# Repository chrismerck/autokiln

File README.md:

# autokiln
Controller for Small Wood-Drying Kilns

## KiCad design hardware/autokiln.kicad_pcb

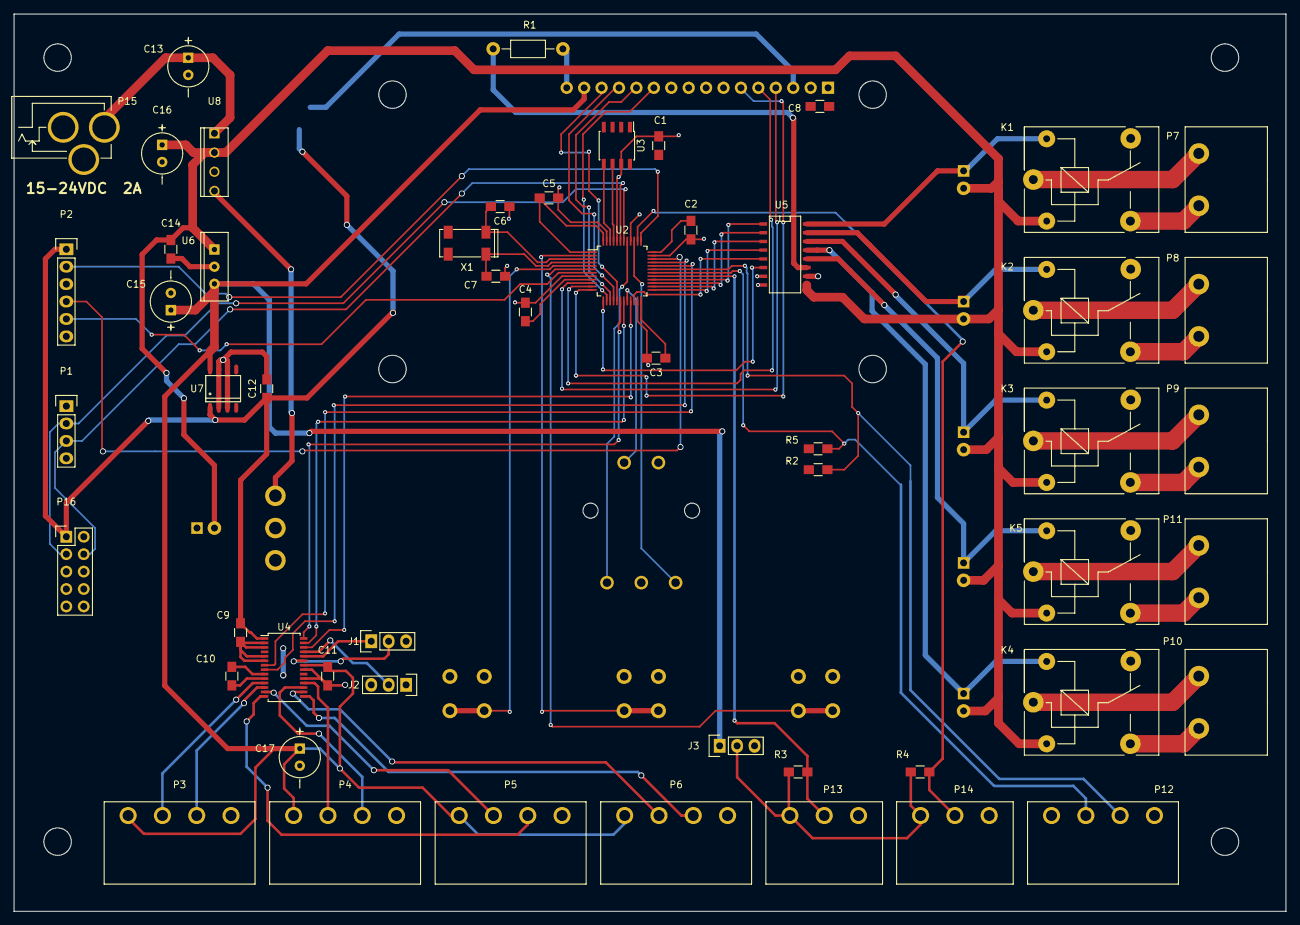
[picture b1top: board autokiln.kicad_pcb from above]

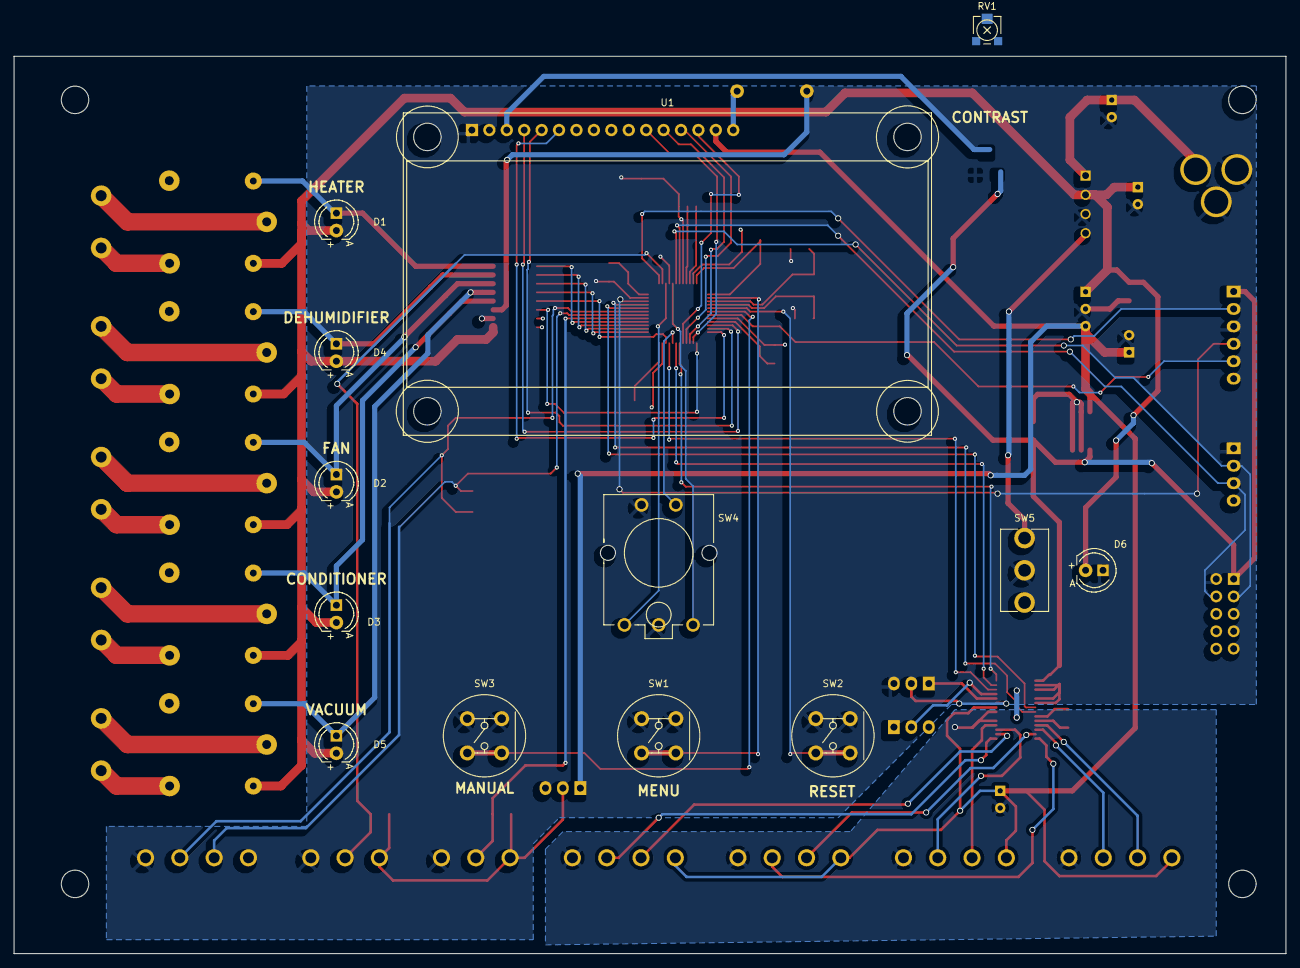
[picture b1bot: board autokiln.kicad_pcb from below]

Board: 2 copper layers, 185.4 x 130.8 mm, 67 parts (13 on the bottom side), 74 nets.

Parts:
C1, C2, C3, C5, C8, C9, C10, C11: 100nF; R_0805_HandSoldering
C4, C12, C14: 4u7; R_0805_HandSoldering
C6, C7: 10pF; R_0805_HandSoldering
C13, C15, C16, C17: 100uF; KEMET_100uF_25V
D1, D2, D3, D4, D5, D6: 12V LED; Diode_LED_5mm_round_vertical
J1: GAIN JUMPER; Pin_Header_Straight_1x03
J2: SPEED JUMPER; Pin_Header_Straight_1x03
J3: HUMID PWR; Pin_Header_Straight_1x03
K1, K2, K3, K4, K5: 12V 250VAC 10A; Relay_SANYOU_SRD_Series_Form_C
P1: DEBUG; Pin_Header_Straight_1x04
P2: SWD; Pin_Header_Straight_1x06
P3: LOAD CELL 1; ostoq047151
P4: LOAD CELL 2; ostoq047151
P5: LOAD CELL 3; ostoq047151
P6: LOAD CELL 4; ostoq047151
P7: HEATER; OSTOQ020151
P8: DEHUMIDIFIER; OSTOQ020151
P9: FAN; OSTOQ020151
P10: VACUUM; OSTOQ020151
P11: CONDITIONER; OSTOQ020151
P12: BAROM; ostoq047151
P13: HUMID1; OSTOQ037151
P14: HUMID2; OSTOQ037151
P15: VIN; CUI_PJ-002AH_DC_PWR_JACK
P16: UEXT; Pin_Header_Straight_2x05
R1: 3; Resistor_Horizontal_RM10mm
R2, R5: 4k7; R_0805_HandSoldering
R3, R4: 1k; R_0805_HandSoldering
RV1: 10K; BOURNS_TRIMMER_3303W
SW1: MENU; CK_Button_D6R
SW2: RESET; CK_Button_D6R
SW3: MANUAL; CK_Button_D6R
SW4: PEC16-4215F-S0024; BOURNS_Encoder_PEC16
SW5: PWR SWITCH; ESwitch-100SP1T1B4M2QE
U1: NHD-0420AZ-FL-YBW-33V3; NHD-0420AZ-FL-GBW-33V3
U2: STM32F070CBT6; LQFP-48_7x7mm_Pitch0.5mm
U3: 24LC512; SOIC-8_3.9x4.9mm_Pitch1.27mm
U4: ADS1234; TSSOP-28_4.4x9.7mm_Pitch0.65mm
U5: ULQ2003; SO-16-N
U6: L7805; TO-220_SG
U7: L4931; SO-8
U8: KA278R12C; TO-220F-4L
X1: 32kHz; Abracon_32KHz

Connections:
+5V: C11.1, C15.1, C17.1, J3.1, P3.1, P4.1, P5.1, P6.1, U1.15, U4.20, U4.22, U6.3, U7.8
+12V: C14.1, C16.1, D1.1, D2.1, D3.1, D4.1, D5.1, D6.1, K1.2, K2.2, K3.2, K4.2, K5.2, U5.9, U6.1, U8.2
/LoadCells/GAIN0: J1.2, U4.23
/LoadCells/LC1N: P3.3, U4.12
/LoadCells/LC1P: P3.2, U4.11
/LoadCells/LC2N: P4.3, U4.17
/LoadCells/LC2P: P4.2, U4.18
/LoadCells/LC3N: P5.3, U4.14
/LoadCells/LC3P: P5.2, U4.13
/LoadCells/LC4N: P6.3, U4.15
/LoadCells/LC4P: P6.2, U4.16
/LoadCells/SPEED: J2.2, U4.25
/Power/VDIS: SW5.1, U8.4
/Relays/DEHUM_COIL: D4.2, K2.5, U5.15
/Relays/FAN_COIL: D2.2, K3.5, U5.14
/Relays/HEATER_COIL: D1.2, K1.5, U5.16
/Relays/STEAM_COIL: D3.2, K5.5, U5.12
/Relays/VACUUM_COIL: D5.2, K4.5, U5.13
/Sensors/HUMID_PWR: J3.2, P13.1, P14.1, R3.2, R4.2
/System/DBG_RX: P1.3, P16.4, U2.43
/System/DBG_TX: P1.2, P16.3, U2.42
/System/ENC_A: SW4.3, U2.39
/System/ENC_B: SW4.5, U2.41
/System/ENC_CLICK: SW4.1, U2.20
/System/LCD_DB4: U1.11, U2.14
/System/LCD_DB5: U1.12, U2.15
/System/LCD_DB6: U1.13, U2.16
/System/LCD_DB7: U1.14, U2.17
/System/LCD_E: U1.6, U2.12
/System/LCD_RS: U1.4, U2.10
/System/LCD_RW: U1.5, U2.11
/System/MANUAL: SW3.1, U2.6
/System/MENU: SW1.1, U2.2
/System/NRST: P2.5, U2.7
/System/OSC32_IN: C6.2, U2.3, X1.1
/System/OSC32_OUT: C7.2, U2.4, X1.2
/System/RESET: SW2.1, U2.5
/System/SWCLK: P2.2, U2.37
/System/SWDIO: P2.4, U2.34
ADC_A0: U2.33, U4.8
ADC_A1: U2.32, U4.7
ADC_DOUT: U2.18, U4.28
ADC_PDWN: U2.21, U4.26
ADC_SCLK: U2.19, U4.27
BAROM_SCL: P12.3, R2.1, U2.31
BAROM_SDA: P12.2, R5.1, U2.30
DEHUM: U2.27, U5.2
FAN: U2.26, U5.3
GND: C1.2, C2.2, C3.2, C4.2, C5.2, C6.1, C7.1, C8.2, C9.2, C11.2, C12.2, C13.2, C14.2, C15.2, C16.2, C17.2, D6.2, J1.3, J2.3, P1.1, P2.3, P3.4, P4.4, P5.4, P6.4, P12.4, P13.3, P14.3, P15.2, P15.3, P16.2, RV1.1, SW1.2, SW2.2, SW3.2, SW4.2, SW4.4, SW5.2, U1.1, U2.8, U2.23, U2.35, U2.44, U2.47, U3.1, U3.2, U3.3, U3.4, U3.7, U4.2, U4.3, U4.5, U4.6, U4.19, U4.21, U5.8, U6.2, U7.2, U7.3, U7.6, U7.7, U8.3
HEATER: U2.28, U5.1
HUMID_DATA1: P13.2, R3.1, U2.29
HUMID_DATA2: P14.2, R4.1, U2.38
LCD_BKL_EN: U2.13, U5.6
LCD_BKL_NEG: R1.1, U5.11
unnamed: C10.1, U4.9
unnamed: C10.2, U4.10
unnamed: C13.1, P15.1, U8.1
unnamed: K1.1, P7.1
unnamed: K1.3, P7.2
unnamed: K2.1, P8.1
unnamed: K2.3, P8.2
unnamed: K3.1, P9.1
unnamed: K3.3, P9.2
unnamed: K4.1, P10.1
unnamed: K4.3, P10.2
unnamed: K5.1, P11.1
unnamed: K5.3, P11.2
unnamed: R1.2, U1.16
unnamed: RV1.2, U1.3
SCL: P16.5, U2.45, U3.6
SDA: P16.6, U2.46, U3.5
STEAM: U2.22, U5.5
VACUUM: U2.25, U5.4
VCC: C1.1, C2.1, C3.1, C4.1, C5.1, C8.1, C9.1, C12.1, J1.1, J2.1, J3.3, P2.1, P12.1, P16.1, R2.2, R5.2, RV1.3, U1.2, U2.1, U2.9, U2.24, U2.36, U2.48, U3.8, U4.1, U4.24, U7.1

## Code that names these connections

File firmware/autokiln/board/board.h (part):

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
// PORT A
#define PPIN_LCD_RS              GPIOA,0
#define PIN_LCD_RS               0
#define PPIN_LCD_RW              GPIOA,1
#define PIN_LCD_RW               1
#define PPIN_LCD_E               GPIOA,2
#define PIN_LCD_E                2
#define PPIN_LCD_BKL_EN          GPIOA,3
#define PIN_LCD_BKL_EN           3
#define PPIN_LCD_DB4             GPIOA,4
#define PIN_LCD_DB4              4
#define PPIN_LCD_DB5             GPIOA,5
#define PIN_LCD_DB5              5
#define PPIN_LCD_DB6             GPIOA,6
#define PIN_LCD_DB6              6
#define PPIN_LCD_DB7             GPIOA,7
#define PIN_LCD_DB7              7
#define PPIN_HUMID_DATA1         GPIOA,8
#define PIN_HUMID_DATA1          8
#define PPIN_BAROM_SDA           GPIOA,9
#define PIN_BAROM_SDA            9
#define PPIN_BAROM_SCL           GPIOA,10
#define PIN_BAROM_SCL            10
#define PPIN_ADC_A1              GPIOA,11
#define PIN_ADC_A1               11
#define PPIN_ADC_A0              GPIOA,12
#define PIN_ADC_A0               12
#define PPIN_SWDIO               GPIOA,13
#define PIN_SWDIO                13
#define PPIN_SWCLK               GPIOA,14
#define PIN_SWCLK                14
#define PPIN_HUMID_DATA2         GPIOA,15
#define PIN_HUMID_DATA2          15

// PORT B
#define PPIN_ADC_DOUT            GPIOB,0
#define PIN_ADC_DOUT             0
#define PPIN_ADC_SCLK            GPIOB,1
#define PIN_ADC_SCLK             1
#define PPIN_ENC_CLICK           GPIOB,2
#define PIN_ENC_CLICK            2
#define PPIN_ENC_A               GPIOB,3
#define PIN_ENC_A                3
#define PPIN_TRST                GPIOB,4 // NC
#define PIN_TRST                 4 // NC
#define PPIN_ENC_B               GPIOB,5
#define PIN_ENC_B                5
#define PPIN_DBG_TX              GPIOB,6
#define PIN_DBG_TX               6
#define PPIN_DBG_RX              GPIOB,7
#define PIN_DBG_RX               7
#define PPIN_SCL                 GPIOB,8
#define PIN_SCL                  8
#define PPIN_SDA                 GPIOB,9
#define PIN_SDA                  9
#define PPIN_ADC_PDWN            GPIOB,10
#define PIN_ADC_PDWN             10
#define PPIN_STEAM               GPIOB,11
#define PIN_STEAM                11
#define PPIN_VACUUM              GPIOB,12
#define PIN_VACUUM               12
#define PPIN_FAN                 GPIOB,13
#define PIN_FAN                  13
#define PPIN_DEHUM               GPIOB,14
#define PIN_DEHUM                14
#define PPIN_HEATER              GPIOB,15
#define PIN_HEATER               15

// PORT C
#define PPIN_MENU                GPIOC,13
#define PIN_MENU                 13
#define PPIN_OSC32_IN            GPIOC,14
#define PIN_OSC32_IN             14
#define PPIN_OSC32_OUT           GPIOC,15
#define PIN_OSC32_OUT            15

// PORT D
// none
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#define PPIN_RESET              GPIOF,0
#define PIN_RESET               0
#define PPIN_MANUAL             GPIOF,1
#define PIN_MANUAL              1

// redirection required for passing port and bit num
#define setPin(PIN)             palSetPad(PIN)
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/*
 * GPIOA setup:
 */
#define VAL_GPIOA_MODER             (PIN_MODE_OUTPUT((PIN_LCD_RS)) |          \
                                     PIN_MODE_OUTPUT((PIN_LCD_RW)) |          \
                                     PIN_MODE_OUTPUT((PIN_LCD_E)) |           \
                                     PIN_MODE_OUTPUT((PIN_LCD_BKL_EN)) |      \
                                     PIN_MODE_INPUT((PIN_LCD_DB4)) |          \
                                     PIN_MODE_INPUT((PIN_LCD_DB5)) |          \
                                     PIN_MODE_INPUT((PIN_LCD_DB6)) |          \
                                     PIN_MODE_INPUT((PIN_LCD_DB7)) |          \
                                     PIN_MODE_OUTPUT((PIN_HUMID_DATA1)) |      \
                                     PIN_MODE_INPUT((PIN_BAROM_SDA)) |        \
                                     PIN_MODE_INPUT((PIN_BAROM_SCL)) |        \
                                     PIN_MODE_OUTPUT((PIN_ADC_A1)) |           \
                                     PIN_MODE_OUTPUT((PIN_ADC_A0)) |           \
                                     PIN_MODE_INPUT((PIN_SWDIO)) |            \
                                     PIN_MODE_INPUT((PIN_SWCLK)) |            \
                                     PIN_MODE_OUTPUT((PIN_HUMID_DATA2)))
#define VAL_GPIOA_OTYPER            (PIN_OTYPE_PUSHPULL((PIN_LCD_RS)) |       \
                                     PIN_OTYPE_PUSHPULL((PIN_LCD_RW)) |       \
                                     PIN_OTYPE_PUSHPULL((PIN_LCD_E)) |        \
                                     PIN_OTYPE_PUSHPULL((PIN_LCD_BKL_EN)) |   \
                                     PIN_OTYPE_PUSHPULL((PIN_LCD_DB4)) |      \
                                     PIN_OTYPE_PUSHPULL((PIN_LCD_DB5)) |      \
                                     PIN_OTYPE_PUSHPULL((PIN_LCD_DB6)) |      \
                                     PIN_OTYPE_PUSHPULL((PIN_LCD_DB7)) |      \
                                     PIN_OTYPE_OPENDRAIN((PIN_HUMID_DATA1)) |  \
                                     PIN_OTYPE_PUSHPULL((PIN_BAROM_SDA)) |    \
                                     PIN_OTYPE_PUSHPULL((PIN_BAROM_SCL)) |    \
                                     PIN_OTYPE_PUSHPULL((PIN_ADC_A1)) |       \
                                     PIN_OTYPE_PUSHPULL((PIN_ADC_A0)) |       \
                                     PIN_OTYPE_PUSHPULL((PIN_SWDIO)) |        \
                                     PIN_OTYPE_PUSHPULL((PIN_SWCLK)) |        \
                                     PIN_OTYPE_OPENDRAIN((PIN_HUMID_DATA2)))
#define VAL_GPIOA_OSPEEDR           (PIN_OSPEED_40M((PIN_LCD_RS)) |           \
                                     PIN_OSPEED_40M((PIN_LCD_RW)) |           \
                                     PIN_OSPEED_40M((PIN_LCD_E)) |            \
                                     PIN_OSPEED_40M((PIN_LCD_BKL_EN)) |       \
                                     PIN_OSPEED_40M((PIN_LCD_DB4)) |          \
                                     PIN_OSPEED_40M((PIN_LCD_DB5)) |          \
                                     PIN_OSPEED_40M((PIN_LCD_DB6)) |          \
                                     PIN_OSPEED_40M((PIN_LCD_DB7)) |          \
                                     PIN_OSPEED_40M((PIN_HUMID_DATA1)) |      \
                                     PIN_OSPEED_40M((PIN_BAROM_SDA)) |        \
                                     PIN_OSPEED_40M((PIN_BAROM_SCL)) |        \
                                     PIN_OSPEED_40M((PIN_ADC_A1)) |           \
                                     PIN_OSPEED_40M((PIN_ADC_A0)) |           \
                                     PIN_OSPEED_40M((PIN_SWDIO)) |            \
                                     PIN_OSPEED_40M((PIN_SWCLK)) |            \
                                     PIN_OSPEED_40M((PIN_HUMID_DATA2)))
#define VAL_GPIOA_PUPDR             (PIN_PUPDR_PULLUP((PIN_LCD_RS)) |         \
                                     PIN_PUPDR_PULLUP((PIN_LCD_RW)) |         \
                                     PIN_PUPDR_PULLUP((PIN_LCD_E)) |          \
                                     PIN_PUPDR_PULLUP((PIN_LCD_BKL_EN)) |     \
                                     PIN_PUPDR_PULLUP((PIN_LCD_DB4)) |        \
                                     PIN_PUPDR_PULLUP((PIN_LCD_DB5)) |        \
                                     PIN_PUPDR_PULLUP((PIN_LCD_DB6)) |        \
                                     PIN_PUPDR_PULLUP((PIN_LCD_DB7)) |        \
                                     PIN_PUPDR_PULLUP((PIN_HUMID_DATA1)) |    \
                                     PIN_PUPDR_PULLUP((PIN_BAROM_SDA)) |      \
                                     PIN_PUPDR_PULLUP((PIN_BAROM_SCL)) |      \
                                     PIN_PUPDR_PULLUP((PIN_ADC_A1)) |         \
                                     PIN_PUPDR_PULLUP((PIN_ADC_A0)) |         \
                                     PIN_PUPDR_PULLUP((PIN_SWDIO)) |          \
                                     PIN_PUPDR_PULLUP((PIN_SWCLK)) |          \
                                     PIN_PUPDR_PULLUP((PIN_HUMID_DATA2)))
#define VAL_GPIOA_ODR               (PIN_ODR_LOW((PIN_LCD_RS)) |             \
                                     PIN_ODR_LOW((PIN_LCD_RW)) |             \
                                     PIN_ODR_LOW((PIN_LCD_E)) |              \
                                     PIN_ODR_LOW((PIN_LCD_BKL_EN)) |         \
                                     PIN_ODR_HIGH((PIN_LCD_DB4)) |            \
                                     PIN_ODR_HIGH((PIN_LCD_DB5)) |            \
                                     PIN_ODR_HIGH((PIN_LCD_DB6)) |            \
                                     PIN_ODR_HIGH((PIN_LCD_DB7)) |            \
                                     PIN_ODR_HIGH((PIN_HUMID_DATA1)) |        \
                                     PIN_ODR_HIGH((PIN_BAROM_SDA)) |          \
                                     PIN_ODR_HIGH((PIN_BAROM_SCL)) |          \
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
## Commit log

2015-03-15 AutoKiln: Initial Commit
    Hardware work in progress
2015-03-21 Schematic Draft Complete
2015-03-22 PCB mostly routed
2015-04-01 PCB updates [wip]
2015-06-04 Autokiln Hardware Rev A
2015-07-04 Autokiln Firmware Initial Commit
    LCD Screen works
    programming works (though awkward)
    ChibiOS 3 checked in alongside
2015-07-04 Autokiln Simulator
    not up to date, but could be used together with real firmware
2015-07-04 Input Events
    Buttons incl. encoder click working
    moving to event-driven design
2015-07-04 Fix LCD line order, splash screen
2015-07-11 Working interrupt for Encoder
2015-07-11 Encoder working (using ISR)
    still need to clean up code
2015-07-11 Send pulses to Humid sensors
    next need to write code to intepret response
2015-07-11 TIM6 operational
2015-07-14 Humid: almost working
    missing some interrupts, need to refactor
2015-07-14 Humid working
    switched from multiple interrupts to single busy loop
    (introduces up to 10ms of latency!!!
2015-07-14 Humid: both sensors working
2015-07-15 ADS1234: Weigh Scale ADC Driver Initial Commit
    can read channel 0
2015-07-15 ADS1234 todo comment
2015-07-18 Menu: Initial Commit
    static for now
2015-07-18 LCD Backlight PWM
    wake, warn, and sleep the backlight
2015-07-18 NV initial commit
    only in ram for now,
    have config menu with changable values
2015-07-18 RTC Tick Working
2015-10-04 Fix Humid checksum calculation

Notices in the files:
firmware/autokiln/board/board.h:
ChibiOS - Copyright (C) 2006..2015 Giovanni Di Sirio
Licensed under the Apache License, Version 2.0 (the "License");
